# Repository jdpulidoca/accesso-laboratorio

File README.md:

# Proyecto Sistemas Embebidos 2022-1 : Control de Acceso para Laboratorios

## Brochure

## Descripción
Como primer idea se plantea un sistema para acceder a un laboratoiro. Se tienen como condiciones que el acceso sea por medio del carnet universitario, donde al acercar el carnet al dispositivo que se diseñara, este desbloqueará la puerta y mostrara los datos en pantalla de la persona que desea ingresar al laboratorio. Este dispositivo activara y desactivara un electroiman que será el encargado de mantener la puerta bloqueada.

## Desarrollo y modelamiento

### Planteamiento Base del Diseño
Para lograr el objetivo del proyecto se plantean las primeras ideas en cuanto a diseño del dispositivo, se plantean las primeras ideas basicas en forma grafica con el fin de ordenar y establecer como  distribuir las tareas que corresponde a Hardware y Software. Esta ideacion esta sujeta a cambios o ajuste debido a las limitaciones del mismo.

### Diagrama de Bloques

### Diagrama de Flujo

### Particionamiento Hardware y Software
#### HardWare
Para esta sección se establecen los siguientes periféricos:  
##### LCD 20x4
EL fin de este periferico es ver la información de la tarjeta con la que se desea ingresar, de igual manera ver si la solicitude de acceso al laboratoirio se aprueba o se denega.

##### PCF8574 Interfaz expansora I^2C
Este modulo se estableció con el fin de generar una comunicación y así verificar los datos obtenidos por medio de la tarjeta entre el sistema implementado y un dispositivo externo.

##### RFID RC522

Este modulo se implementa con el fin de leer los datos aportados por la tarjeta

##### Rele 5V Forma C

Este modulo se implementa para aislar la señal digital que nos da o nos niega el acceso de la puerta

##### Modulo ESP32 WROOM

Como último se tiene la tarjeta ESP32 desde donde se controlan los demás modulos, se implementa el codigo referente al proyecto

##### Fuente de Alimentacion

Se plantean 2 soluciones para la alimentación del sistema, como primer solución se tiene una fuente variable que corresponde al de la siguiente imagen.

###### Fuente 12 V

###### Bateria 12 V

Como segunda solución se plantea la implementación de una bateria extraida de una motocicleta, la cual se puede ver en la siguiente imagen

#### SoftWare
##### Codigo

### Esquema del Diseño

Este se divide en 4 "Islas" principales, divididos segun los valores de alimentacion. 

En primera instancia se se tienen los componetes que operan a con 3.3 V

En la siguiente imagen se muestra las conecciones a la ESP32, puertos de programación y adicional a esto tambien se puede evidenciar las conecciones del modulo RFID

Para la siguiente imagen se tienen las conecciones correspondientes a I2C para las pantallas LCD

Coneccion del rele con su respectivo controlador con el fin de activarlo con 3.3v y dar acceso al sistema

Y por ultimo tenemos un sistema de fuentes lineales con el cual podemos reducir la tensión de 12v a 5v y de 5v a 3.3. Este mismo cambio de fuente a bateria en caso de una interrupción en la alimentación

### Diseño del Circuito Impreso

Se muestra el prototipo que se obtendra al imprimir la tarjeta y los dispositivos a soldar

### Error de Diseño
### Proceso de Compra

Despues de terminar el diseño de la PCB se empieza a estuiar los posibles proveedores para mandar imprimir dicha placa, con lo que se decide mandarla imprimir en JLCPBC

Seguido a esto se carga el diseño y se confirma la compra, la compra se realiza con tarjeta de debito.

En las siguientes imagenes se observara el proceso de compra paso a paso

Se seleccionan las diferentes caracteristicas referentes a la PCB y a los datos de envio, tambien se evidencian los costos e impuestos adicionales que no se tenían previstos.

Datos de envio

Valor estimado

Se modifica el archivo de elementos que se solicitaron soldar ya que la pagina solicitaba un formato especifico para poder ser procesado. Adicional a esto se escogen los dispositivos donde se tratan de adecuar a la necesidad del proyecto y al presupuesto

Se adjunta evidencia del proceso de compra

Se muestra la factura del impuesto adicional que toca pagar al llegar el paquete. este impuesto se entiende como un proceso de nacionalización del producto ya que Colombia no posee tratado de libre comercio con china.

## Pruebas
Las pruebas se realizaron sobre 2 tajetas. En primer lugar se trabajo con una tarjeta  experimental, que consiste en una baquelita solda donde se probaron los perifericos mediantes una tarjeta de desarrollo ESP32 DEVKIT V1. Una vez comprobado el funcionamiento de los perifericos y el codigo en la tarjeta experimental, se procede a aplicarlo en la PCB diseñada y realizar los cambios pertinentes para lograr las tares que se requieren.
### Experimental

Primero se prueban cada uno de los perifericos con el fin de verificar que esten en buen estado como se muestran en las siguientes imagenes

Empezamos adecuando un ESP32 para hacer las pruebas

Seguido a esto probamos el modulo RFID

Pruebas en bateria y fuente

Se conectan los modulos RFID y la pantalla LCD

### Diseñada

## Funcionamiento

Al conectar los diferentes perifericos junto a la PCB se tiene que al acercar una tarjeta autorizada los datos de la tarjeta llegarán a la pantalla y el dispositivo dará acceso de entrada a la puerta. Por otro lado, cuando se acerque una tarjeta no autorizada igualmente se tendrán los datos en pantalla junto al mensaje de acceso denegado, pero en esta ocasión no se dará acceso a la puerta.

## Resultados

Como resultados a las pruebas se realizaron diferentes pruebas.

La primer prueba realizada para probar el modulo RFID, donde se identifica que se han podido leer los datos de las tarjetas y se evidencia que se tiene la respuesta segun dado el nivel de acceso de latrjeta. Se grabaron los siguientes videos:

Despues de haber implementado los diferentes modulos se realizan las siguientes pruebas y se mostraran los resultados obtenidos

### Prototipo

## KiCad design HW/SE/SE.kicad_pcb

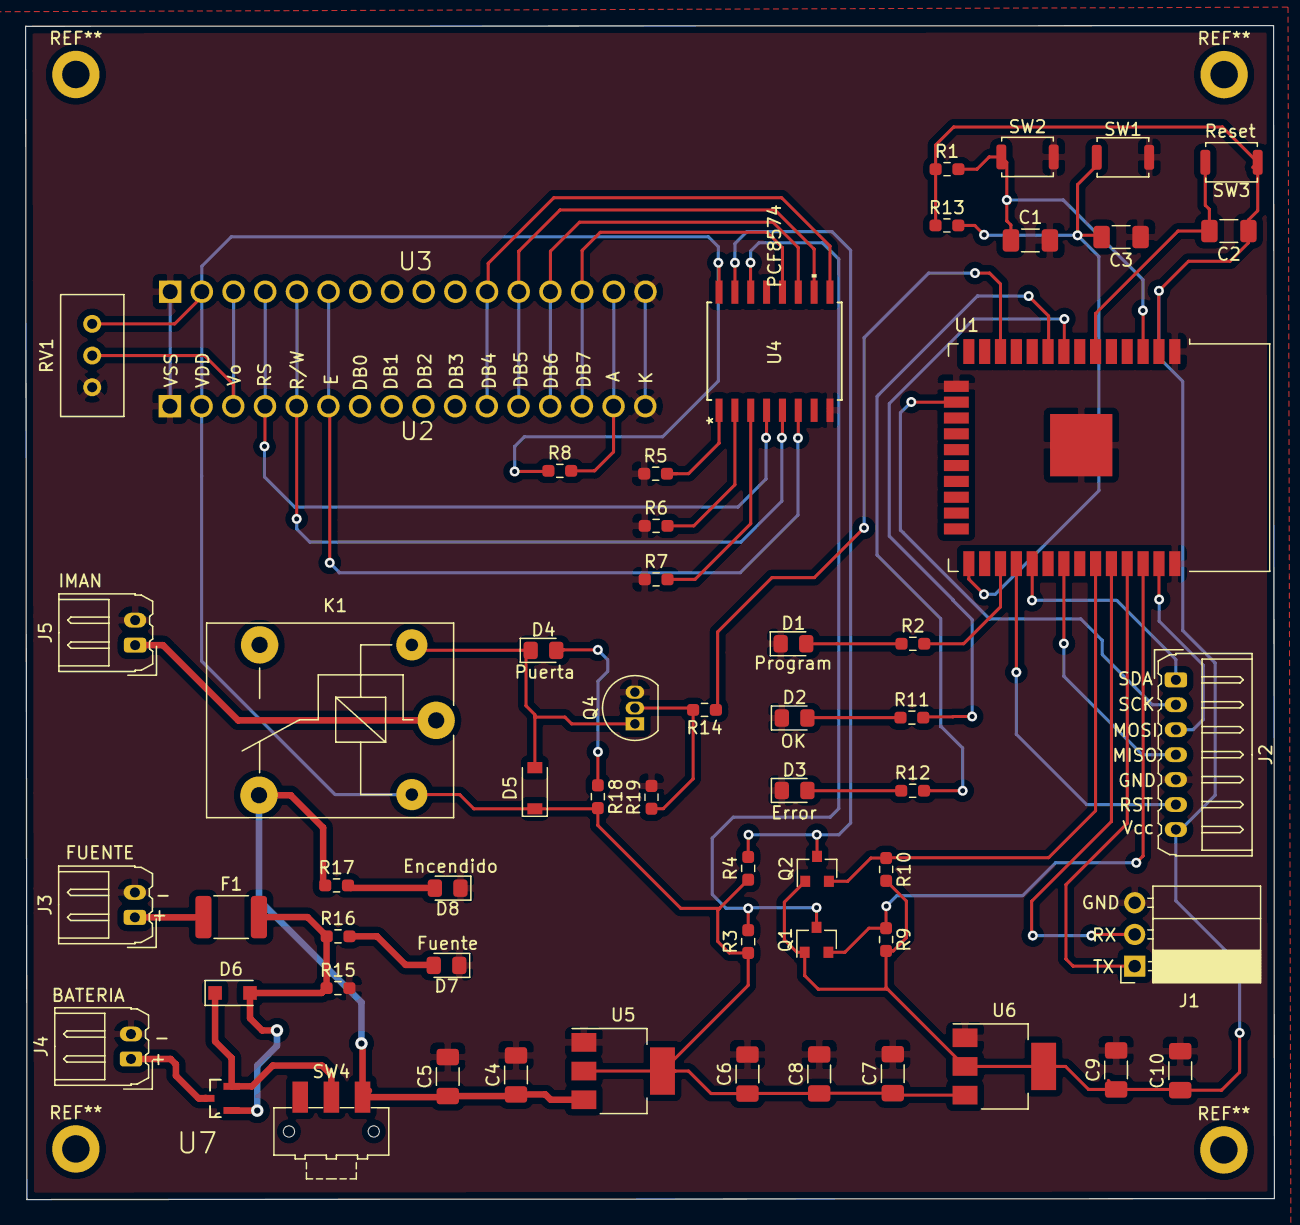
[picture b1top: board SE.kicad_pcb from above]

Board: 2 copper layers, 100.1 x 94.1 mm, 59 parts (0 on the bottom side), 47 nets.

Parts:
C1, C2, C3: 10u; C_1206_3216Metric_Pad1.33x1.80mm_HandSolder
C4, C8, C10: 100n; C_1206_3216Metric_Pad1.33x1.80mm_HandSolder
C5, C6: 100u; C_1206_3216Metric_Pad1.33x1.80mm_HandSolder
C7, C9: 22u; C_1206_3216Metric_Pad1.33x1.80mm_HandSolder
D1, D2, D3, D4, D7, D8: LED; LED_0805_2012Metric_Pad1.15x1.40mm_HandSolder
D5: 1N4148W; D_SOD-123
D6: MBR1020VL; D_SOD-123F
F1: Fuse; Fuse_1812_4532Metric_Pad1.30x3.40mm_HandSolder
J1: Conn_01x03_Female; PinSocket_1x03_P2.54mm_Horizontal
J2: Conn_01x07_Female; Molex_Micro-Latch_53254-0770_1x07_P2.00mm_Horizontal
J3, J4, J5: Conn_01x02_Female; Molex_Micro-Latch_53254-0270_1x02_P2.00mm_Horizontal
K1: SANYOU_SRD_Form_C; Relay_SPDT_SANYOU_SRD_Series_Form_C
Q1, Q2: BSS138; SOT-23
Q4: BC548; TO-92_Inline
R1, R3, R4, R9, R10, R13: 10k; R_0603_1608Metric_Pad0.98x0.95mm_HandSolder
R2, R11, R12: 220; R_0603_1608Metric_Pad0.98x0.95mm_HandSolder
R5, R6, R7, R15, R19: 100k; R_0603_1608Metric_Pad0.98x0.95mm_HandSolder
R8: 330; R_0603_1608Metric_Pad0.98x0.95mm_HandSolder
R14: 1.2k; R_0603_1608Metric_Pad0.98x0.95mm_HandSolder
R16, R17: 1k; R_0603_1608Metric_Pad0.98x0.95mm_HandSolder
R18: 1.8k; R_0603_1608Metric_Pad0.98x0.95mm_HandSolder
RV1: 10k; Potentiometer_Bourns_3296W_Vertical
SW1: Program; SW_Push_SPST_NO_Alps_SKRK
SW2: ResetP; SW_Push_SPST_NO_Alps_SKRK
SW3: Reset; SW_Push_SPST_NO_Alps_SKRK
SW4: SW_DPDT_x2; SW_SPDT_CK-JS102011SAQN
U1: ESP32-WROOM-32
U2, U3: NHD-0420H1Z; LCD_LCD-20X4B
U4: PCF8574; PCF8574ADWR_DW16
U5: AMS1117-5.0; SOT-223-3_TabPin2
U6: AMS1117-3.3; SOT-223-3_TabPin2
U7: DMG3415U-7; SOT95P240X105-3N

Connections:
+3V3: C2.1, C9.1, C10.1, J2.7, Q1.1, Q2.1, R1.1, R9.2, R10.2, R13.1, SW3.1, U1.2, U6.2
+5V: C6.1, C7.1, C8.1, D5.1, K1.5, R3.1, R4.1, R8.1, R18.2, RV1.1, U2.2, U3.2, U4.16, U5.2, U6.3
+12V: C4.1, C5.1, K1.4, R17.1, SW4.3, U5.3
Crelay: R14.1, U1.12
GND: C1.2, C3.1, C4.2, C5.2, C6.2, C7.2, C8.2, C9.2, C10.2, D1.1, D2.1, D3.1, D7.1, D8.1, J1.3, J2.5, J3.2, J4.2, J5.2, Q4.3, R5.1, R6.1, R7.1, R15.2, R19.2, RV1.3, SW1.2, SW2.2, U1.1, U1.15, U1.38, U1.39, U2.1, U2.16, U3.1, U3.16, U4.8, U5.1, U6.1
unnamed: C1.1, R1.2, SW2.1, U1.3
unnamed: C2.2, SW3.2, U1.6
unnamed: C3.2, R13.2, SW1.1, U1.25
unnamed: D1.2, R2.1
unnamed: D2.2, R11.1
unnamed: D3.2, R12.1
unnamed: D4.1, D5.2, K1.2, Q4.1
unnamed: D4.2, R18.1
unnamed: D6.1, SW4.2, U7.2
unnamed: D6.2, F1.2, R15.1, R16.1, U7.1
unnamed: D7.2, R16.2
unnamed: D8.2, R17.2
unnamed: F1.1, J3.1
unnamed: J1.1, U1.35
unnamed: J1.2, U1.34
unnamed: J2.1, U1.29
unnamed: J2.2, U1.16
unnamed: J2.3, U1.37
unnamed: J2.4, U1.31
unnamed: J2.6, U1.28
unnamed: J5.1, K1.1
unnamed: Q1.3, R3.2, U4.14
unnamed: Q2.3, R4.2, U4.15
unnamed: Q4.2, R14.2, R19.1
unnamed: R2.2, U1.27
unnamed: R5.2, U4.1
unnamed: R6.2, U4.2
unnamed: R7.2, U4.3
unnamed: R8.2, U2.15, U3.15
unnamed: R11.2, U1.8
unnamed: R12.2, U1.9
unnamed: RV1.2, U2.3, U3.3
unnamed: U2.4, U3.4, U4.4
unnamed: U2.5, U3.5, U4.5
unnamed: U2.6, U3.6, U4.6
unnamed: U2.11, U3.11, U4.9
unnamed: U2.12, U3.12, U4.10
unnamed: U2.13, U3.13, U4.11
unnamed: U2.14, U3.14, U4.12
SCL: Q1.2, R9.1, U1.36
SDA: Q2.2, R10.1, U1.33
Vbat: J4.1, U7.3

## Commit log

2022-04-09 Creación Carpeta Imágenes
2022-04-09 Ideacion
2022-04-09 Planteamiento Basico
2022-04-09 Nombre muy largo
2022-04-09 Por crear la carpeta
2022-04-28 Inicio Esquematico
2022-05-05 AJustes Dsiplay
2022-05-05 Control REle y entrada sensnores
2022-05-10 Ajustes
2022-05-12 Primer diseño fuente
2022-05-15 Esquematico Completo
2022-05-17 Ajustes Esquematico y Seleccion FootPrint
2022-05-17 Uso Flag de fuente
2022-05-17 Correccion Esquematico
2022-05-17 Asignacion FootPrint e inicio PCB
2022-05-24 Inicio PCB
2022-05-24 Ajuste PCB
2022-05-24 Distribucion final de componetes en 10*10
2022-05-24 Calculo pista 12V
2022-05-24 Conecciones Iniciales
2022-05-25 Ruteo y dimensionamiento
2022-05-25 PCB lista
2022-05-25 Nombramiento puertos y testigos
2022-05-27 Ajustes Finales PCB
2022-05-31 Dimensiones agujeros de agarre PCB
2022-06-07 Distribución Wiki
2022-06-07 Pdf esquematico
2022-06-26 Ensayo Editor Visual Studio
2022-06-26 Inicio descripción esquemático
2022-07-04 Distribución Pistas
2022-07-05 PlanoT
2022-07-05 PlanoTC
2022-07-05 Proceso de Compra
2022-07-05 Primeras Pruebas
2022-07-05 ZonaC
2022-07-05 SoftWare
2022-07-06 Diagrama de bloques
2022-07-06 Diagrama de Flujo
2022-07-06 Videos
2022-07-06 Mas Multimedia
2022-07-06 Brochure
